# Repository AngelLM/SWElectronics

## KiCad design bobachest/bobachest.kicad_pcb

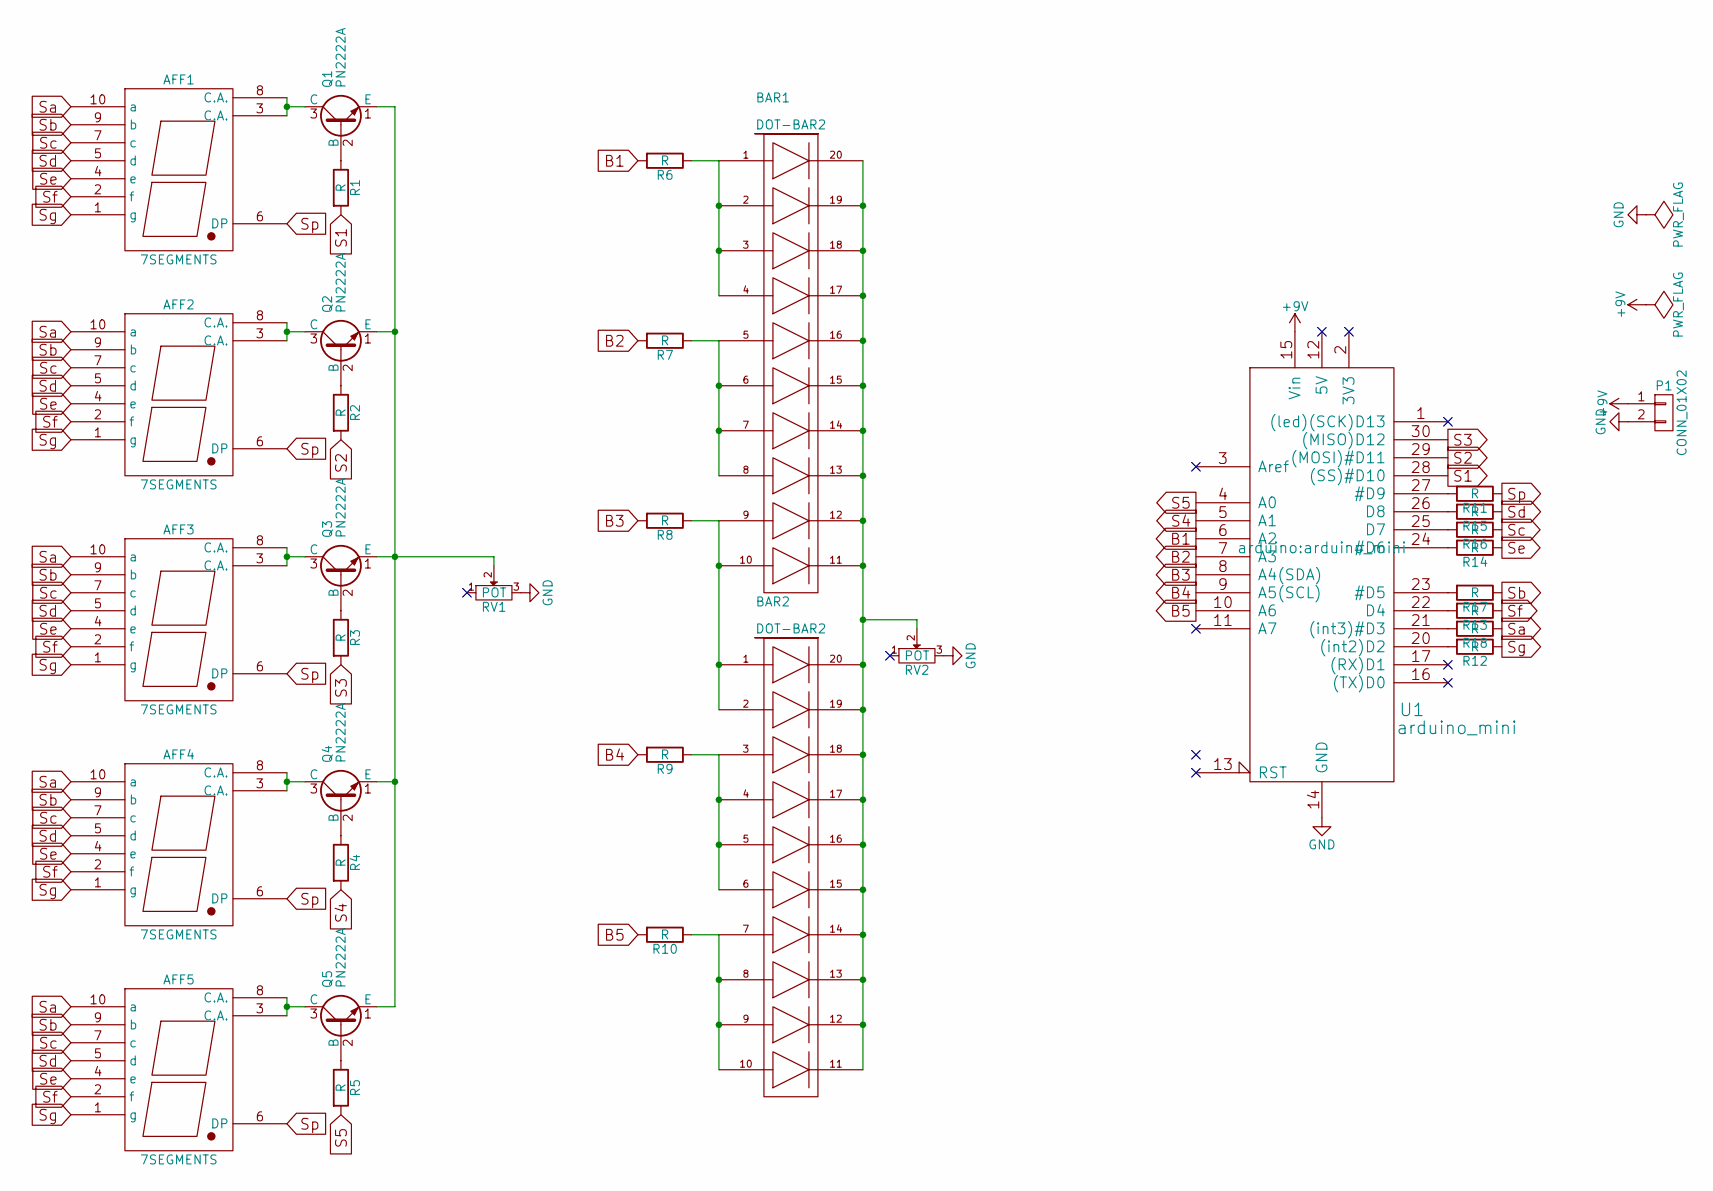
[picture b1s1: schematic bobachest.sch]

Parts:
AFF1, AFF2, AFF3, AFF4, AFF5: 7SEGMENTS; 7Segment9.9
BAR1, BAR2: DOT-BAR2; HDSP-48xx
P1: CONN_01X02; Pin_Header_Straight_1x02
Q1, Q2, Q3, Q4, Q5: PN2222A; TO-92_Inline_Narrow_Oval
R1, R2, R3, R4, R5, R6, R7, R8, R9, R10, R11, R12, R13, R14, R15, R16, R17, R18: R; Resistor_Horizontal_RM7mm
RV1, RV2: POT; Potentiometer_Trimmer-Suntan-TSR-3386P
U1: arduino_mini

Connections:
+9V: P1.1, U1.15 (Vin)
B1: R6.2, U1.6 (A2)
B2: R7.2, U1.7 (A3)
B3: R8.2, U1.8 (A4(SDA))
B4: R9.2, U1.9 (A5(SCL))
B5: R10.2, U1.10 (A6)
GND: P1.2, RV1.3, RV2.3, U1.14 (GND), U1.19 (GND)
unnamed: AFF1.3 (C.A.), AFF1.8 (C.A.), Q1.3 (C)
unnamed: AFF2.3 (C.A.), AFF2.8 (C.A.), Q2.3 (C)
unnamed: AFF3.3 (C.A.), AFF3.8 (C.A.), Q3.3 (C)
unnamed: AFF4.3 (C.A.), AFF4.8 (C.A.), Q4.3 (C)
unnamed: AFF5.3 (C.A.), AFF5.8 (C.A.), Q5.3 (C)
unnamed: BAR1.1 (A), BAR1.2 (A), BAR1.3 (A), BAR1.4 (A), R6.1
unnamed: BAR1.5 (A), BAR1.6 (A), BAR1.7 (A), BAR1.8 (A), R7.1
unnamed: BAR1.9 (A), BAR1.10 (A), BAR2.1 (A), BAR2.2 (A), R8.1
unnamed: BAR1.11 (K), BAR1.12 (K), BAR1.13 (K), BAR1.14 (K), BAR1.15 (K), BAR1.16 (K), BAR1.17 (K), BAR1.18 (K), BAR1.19 (K), BAR1.20 (K), BAR2.11 (K), BAR2.12 (K), BAR2.13 (K), BAR2.14 (K), BAR2.15 (K), BAR2.16 (K), BAR2.17 (K), BAR2.18 (K), BAR2.19 (K), BAR2.20 (K), RV2.2
unnamed: BAR2.3 (A), BAR2.4 (A), BAR2.5 (A), BAR2.6 (A), R9.1
unnamed: BAR2.7 (A), BAR2.8 (A), BAR2.9 (A), BAR2.10 (A), R10.1
unnamed: Q1.1 (E), Q2.1 (E), Q3.1 (E), Q4.1 (E), Q5.1 (E), RV1.2
unnamed: Q1.2 (B), R1.1
unnamed: Q2.2 (B), R2.1
unnamed: Q3.2 (B), R3.1
unnamed: Q4.2 (B), R4.1
unnamed: Q5.2 (B), R5.1
unnamed: R11.2, U1.27 (#D9)
unnamed: R12.2, U1.20 ((int2)D2)
unnamed: R13.2, U1.22 (D4)
unnamed: R14.2, U1.24 (#D6)
unnamed: R15.2, U1.26 (D8)
unnamed: R16.2, U1.25 (D7)
unnamed: R17.2, U1.23 (#D5)
unnamed: R18.2, U1.21 ((int3)#D3)
S1: R1.2, U1.28 ((SS)#D10)
S2: R2.2, U1.29 ((MOSI)#D11)
S3: R3.2, U1.30 ((MISO)D12)
S4: R4.2, U1.5 (A1)
S5: R5.2, U1.4 (A0)
Sa: AFF1.10 (a), AFF2.10 (a), AFF3.10 (a), AFF4.10 (a), AFF5.10 (a), R18.1
Sb: AFF1.9 (b), AFF2.9 (b), AFF3.9 (b), AFF4.9 (b), AFF5.9 (b), R17.1
Sc: AFF1.7 (c), AFF2.7 (c), AFF3.7 (c), AFF4.7 (c), AFF5.7 (c), R16.1
Sd: AFF1.5 (d), AFF2.5 (d), AFF3.5 (d), AFF4.5 (d), AFF5.5 (d), R15.1
Se: AFF1.4 (e), AFF2.4 (e), AFF3.4 (e), AFF4.4 (e), AFF5.4 (e), R14.1
Sf: AFF1.2 (f), AFF2.2 (f), AFF3.2 (f), AFF4.2 (f), AFF5.2 (f), R13.1
Sg: AFF1.1 (g), AFF2.1 (g), AFF3.1 (g), AFF4.1 (g), AFF5.1 (g), R12.1
Sp: AFF1.6 (DP), AFF2.6 (DP), AFF3.6 (DP), AFF4.6 (DP), AFF5.6 (DP), R11.1

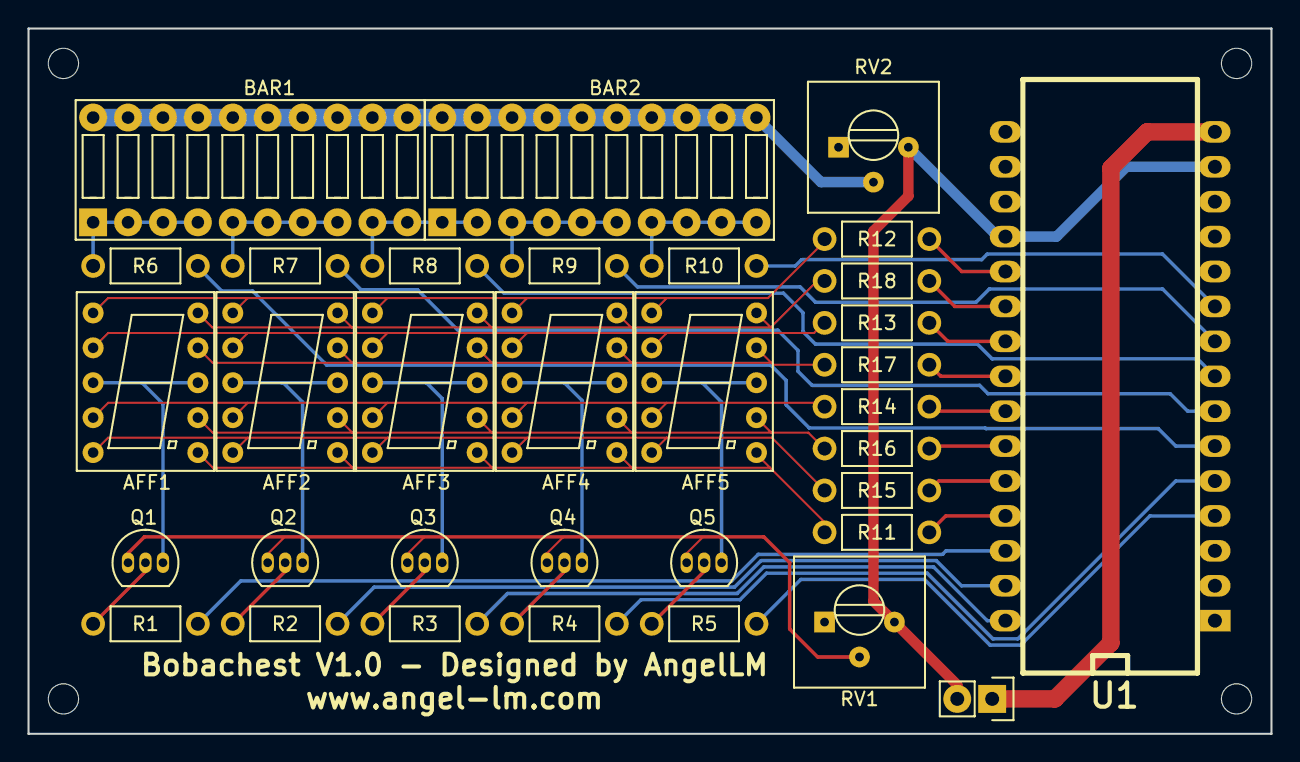
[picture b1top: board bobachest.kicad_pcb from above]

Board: 2 copper layers, 90.4 x 51.3 mm, 34 parts (0 on the bottom side), 45 nets.

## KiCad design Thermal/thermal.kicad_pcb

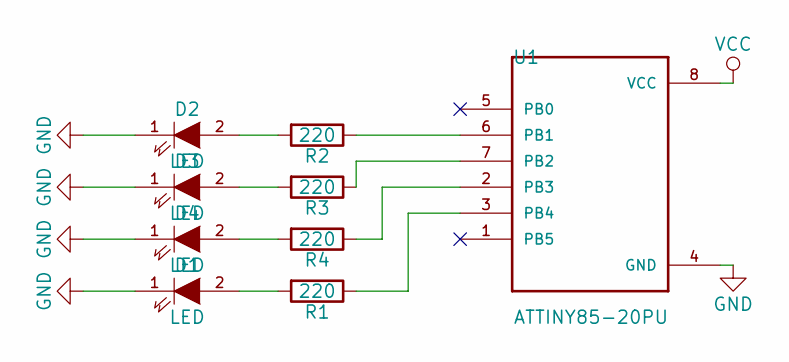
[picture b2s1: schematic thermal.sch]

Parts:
D1, D2, D3, D4: LED; LED-5MM
R1, R2, R3, R4: 220; Resistor_TO-220_Horizontal
U1: ATTINY85-20PU; DIP762W46P254L927H533Q8B

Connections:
GND: D1.1 (K), D2.1 (K), D3.1 (K), D4.1 (K), U1.4 (GND)
unnamed: D1.2 (A), R1.2
unnamed: D2.2 (A), R2.2
unnamed: D3.2 (A), R3.2
unnamed: D4.2 (A), R4.2
unnamed: R1.1, U1.3 (PB4)
unnamed: R2.1, U1.6 (PB1)
unnamed: R3.1, U1.7 (PB2)
unnamed: R4.1, U1.2 (PB3)
VCC: U1.8 (VCC)

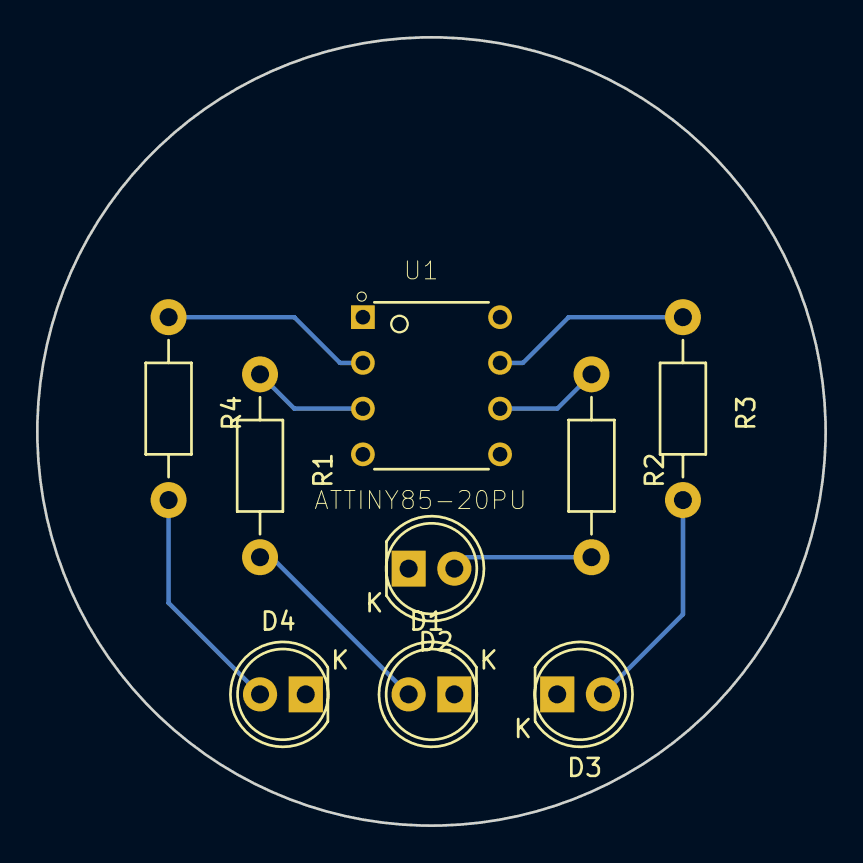
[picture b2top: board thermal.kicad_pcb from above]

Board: 2 copper layers, 43.8 x 43.8 mm, 9 parts (0 on the bottom side), 9 nets.

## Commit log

2016-12-02 Upload
2016-12-07 Bobachest update
2016-12-08 gerber files
2016-12-13 Arduino files
2016-12-14 Color changes
2017-02-08 Arduino update
2017-10-06 random add
